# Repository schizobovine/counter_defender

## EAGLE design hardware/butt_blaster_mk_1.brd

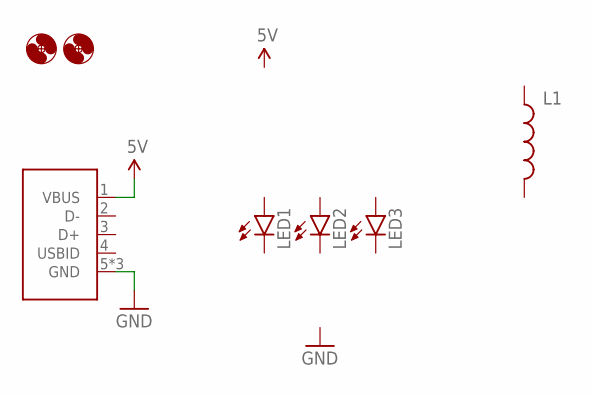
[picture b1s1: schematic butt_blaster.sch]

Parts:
H1, H2: HOLE#2; HOLE-#2
L1: INDUCTORAXIAL-PTH-7.68MM; INDUCTOR-AXIAL-PTH-7.68MM
LED1, LED2, LED3: LED5MM_SHORTPADS
U1: USB-ABCOMBO; USB-MICRO-B-FCI-CUTOUT

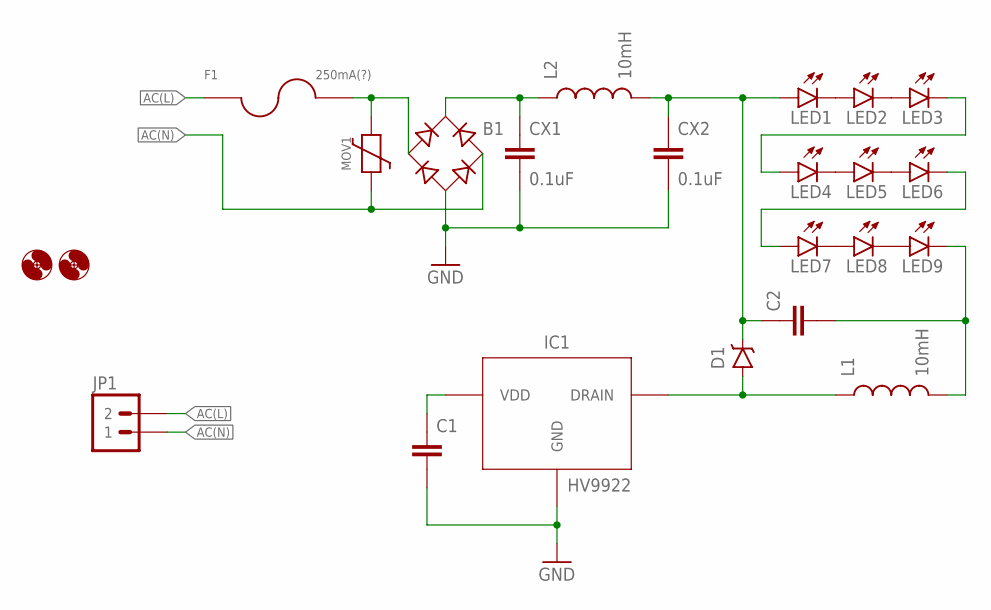
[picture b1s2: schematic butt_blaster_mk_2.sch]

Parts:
B1: RB1ANOSUCK; RB1A-NOSUCK
C1, C2: CAPACITOR-CERAMIC025-024X044; C025-024X044
CX1, CX2: 0.1uF; XC10B5
D1: DIODE-SCHOTTKYPTH-7.68MM; DIODE-7.68MM
F1: 250mA(?); TR5
H1, H2: HOLE#2; HOLE-#2
IC1: HV9922; TO-92
JP1: M025MM; SCREWTERMINAL-5MM-2
L1: 10mH; RLB0912
L2: 10mH; INDUCTOR-AXIAL-PTH-10.16MM
LED1, LED2, LED3, LED4, LED5, LED6, LED7, LED8, LED9: LED5MM_SHORTPADS
MOV1: VARISITORVAR-5.08MM-PTH; VAR-5.08MM-PTH

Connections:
AC(L): F1.1, JP1.2
AC(N): B1.AC2, JP1.1, MOV1.1
GND: B1.-, C1.2, CX1.2, CX2.2, IC1.2 (GND)
unnamed: LED1.K (C), LED2.A
unnamed: LED2.K (C), LED3.A
unnamed: LED4.K (C), LED5.A
unnamed: LED5.K (C), LED6.A
unnamed: LED3.K (C), LED4.A
unnamed: LED6.K (C), LED7.A
unnamed: LED7.K (C), LED8.A
unnamed: LED8.K (C), LED9.A
unnamed: C2.2, L1.2, LED9.K (C)
unnamed: D1.A, IC1.1 (DRAIN), L1.1
unnamed: C2.1, CX2.1, D1.K (C), L2.P$2 (2), LED1.A
unnamed: B1.AC1, F1.2, MOV1.2
unnamed: B1.+, CX1.1, L2.P$1 (1)
unnamed: C1.1, IC1.3 (VDD)

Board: 2 copper layers, 23 parts (0 on the bottom side), 17 nets, no tracks yet.
